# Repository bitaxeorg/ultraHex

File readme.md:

Warning: the bitaxeHex is unfinished. there may be hardware and firmware bugs. Please see The bitaxeHex channel on the [OSMU Discord](https://discord.gg/osmu) for the latest status

> Closed Source is Antithetical to Bitcoin

# Presenting: The bitaxeHex
bitaxeHex is a follow on to the [bitaxe](https://github.com/skot/bitaxe) that incorporates six BM1366 ASICs from the Antminer S19XP

## Goals
- **Standalone**: can mine directly to your pool over WiFi. No External computer needed.
- **Embedded**: low cost, low maintenance, high availability, high reliability, low power.
- **ASIC**: based on the very efficient BM1366 from Bitmain.
- **Versatile**: solo/pool mining, autotune power/heat/efficiency.
- **Open Source**: All design files are provided.

## Features
- **ESP32-S3-WROOM-1** wifi microcontroller on board
- **TI TPS546D24ARVFR** buck regulator steps down the 12V input to power the chain of BM1366
- **TMP1075** measures inlet and outlet PCB temperature.
- **Microchip EMC2302** Controls dual fans
- Header for optional status LCD

## BM1366
- The BM1366 is a undocumented SHA256 mining ASIC from Bitmain. It's mostly used in the Antminer S19XP and S19K Pro
- Bitmain claims the BM1366 has 21.5 W/TH efficiency
- The BM1366 is available (new) for around $15 each.

## Current Status
- v304 is the latest revision but it has a known problem with the Vcore regulator.  There is a workaround, see the bottom of this readme.
- Power draw is around 50W @12V.
- ESP32 miner firmware will configure the power supply to run at the proper voltage.
- This is an _advanced_ build! If you don't have experience building boards, you should probably go build a single ASIC bitaxe first to get the technique down.

## Notes
- Beware that overclocking doesn't produce a higher hash rate on this board, it only causes more heat generation.
- If you decide to build a pre-release board, be sure to order 2 oz. copper on both the internal and external layers.
- The recommended heatsink is not anodized and very conductive on all surfaces. This _should_ be OK as the ASIC tops are not known to be conductive, but this needs some more investigation.

## Revision List
- v304 has a few new minor features, but it has a problem with the Vcore output capacitance.
- v303 has some improvements in the layout and the 33R inline resistors have been removed.
- V302 is the current working version of this board.  If you want to build this, pull down this git tag.
- V301 does not work, the power supply maintains voltage, but overheats in a drastic way
- V300 does not work, the power supply cannot maintain voltage when a load is applied

## Hardware
- [BM1366 from NBTC on AliExpress](https://www.aliexpress.us/item/3256803471845503.html). Both the `AL` and `AG` variants have been known to work.
- [Heatsink](https://www.aliexpress.us/item/3256805608902122.html) 90mm long variant. This will need to have threaded M3 mounting holes added. See the KiCad board file for the pattern
- [Fans](https://www.amazon.com/Noctua-NF-A8-PWM-Premium-Quiet/dp/B00NEMG62M) At least one 80x80mm 12V 4-pin fan. Like the Noctua NF-A8 PWM. Possibly two.
- [Enclosure](https://www.aliexpress.us/item/3256806064761702.html) (several sellers) 130mm long variant. The bitaxeHex needs to be run inside an enclosure to force air through the heatsink and effectively cool the BM1366s
- The TPS546 can potentially benefit from a [small self-adhesive heatsink](https://www.amazon.com/gp/product/B093V6RK58/) on the top of the package.
- All of the parts on the board are listed in the KiCad BOM

## Software
- [ESP-Miner-multichip](https://github.com/bitaxeorg/esp-miner-multichip) a fork of esp-miner to support multiple ASICs like on the bitaxeHex.

## Power Supply Requirements
- bitaxeHex takes 12V DC input via screw terminals. Power supply should be capable of 100W
  - This [120W Brick](https://www.amazon.com/gp/product/B07PWZQ33N) technically works, but gets a little warmer than it should. You'll need to change the end.
  - 12V 15A 110V AliExpress [Bare PSU](https://www.aliexpress.us/item/3256805439916551.html)

## Building
- Check out [building.md](building.md) for PCB ordering tips
- Check out [assembly.md](assembly.md) for assembly tips

## V304 Modification
The Vcore regulator output doesn't have enough bulk capacitance, and the regulator won't run in a stable mode.
In order to fix this, you can hack on a couple 180 uF Aluminium Polymer electrolytic capacitors.  See this diagram for the schematic and part numbers.  The specified parts have wire leads, and you can solder one on each side of the board across the existing ceramic output caps.

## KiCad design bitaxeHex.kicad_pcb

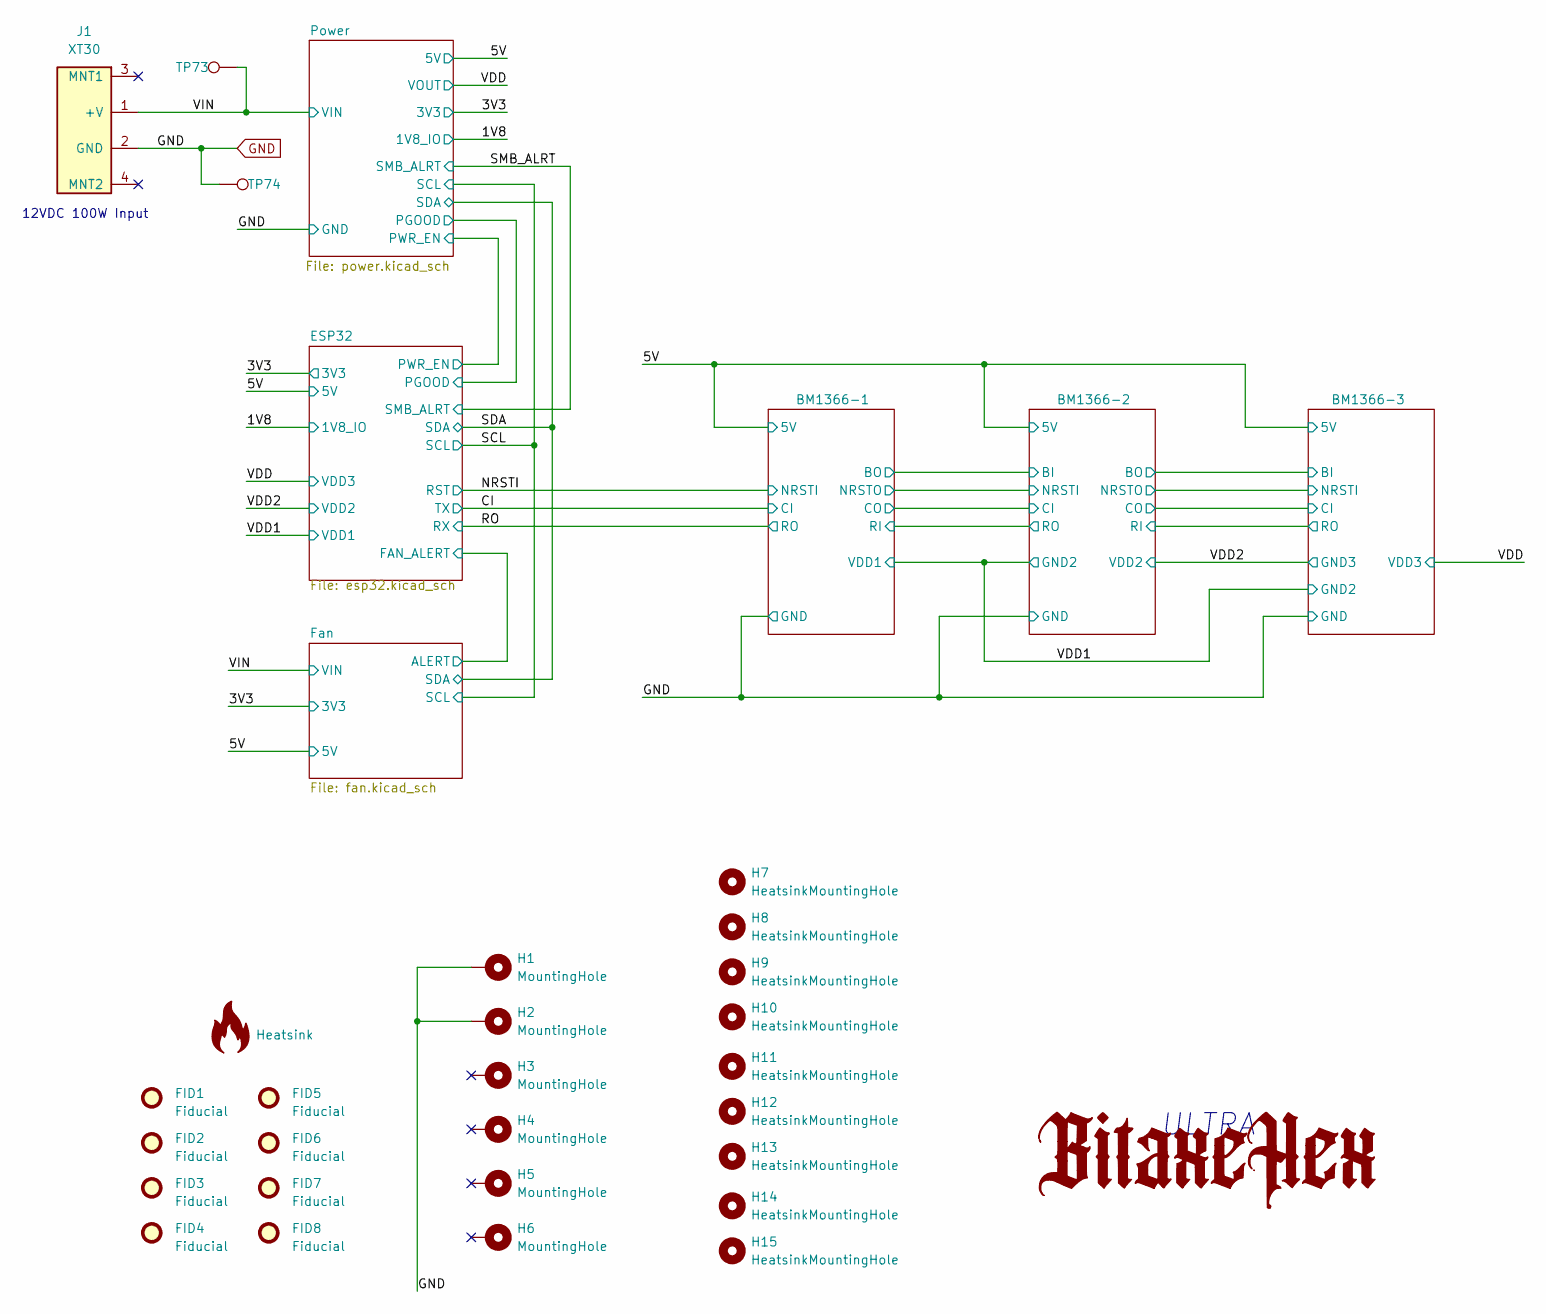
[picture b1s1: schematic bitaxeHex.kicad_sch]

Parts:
FID1, FID2, FID3, FID4, FID5, FID6, FID7, FID8: Fiducial; Fiducial_1mm_Mask2mm
H1, H2, H3, H4, H5, H6: MountingHole; MountingHole_3mm_Pad_Via
H7, H8, H9, H10, H11, H12, H13, H14, H15: HeatsinkMountingHole; 3.1mm_mounting
HS1: Heatsink; hex-heatsink
J1: XT30; XT30PW-M; PARTNO XT30PW-M
TP73, TP74: TestPoint; TestPoint_Pad_D1.0mm

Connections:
/VIN: J1.1 (+V), TP73.1 (1_1); also elsewhere on the board
GND: H1.1 (1_1), H2.1 (1_1), J1.2 (GND), TP74.1 (1_1); also elsewhere on the board

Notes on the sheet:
ULTRA
12VDC 100W Input

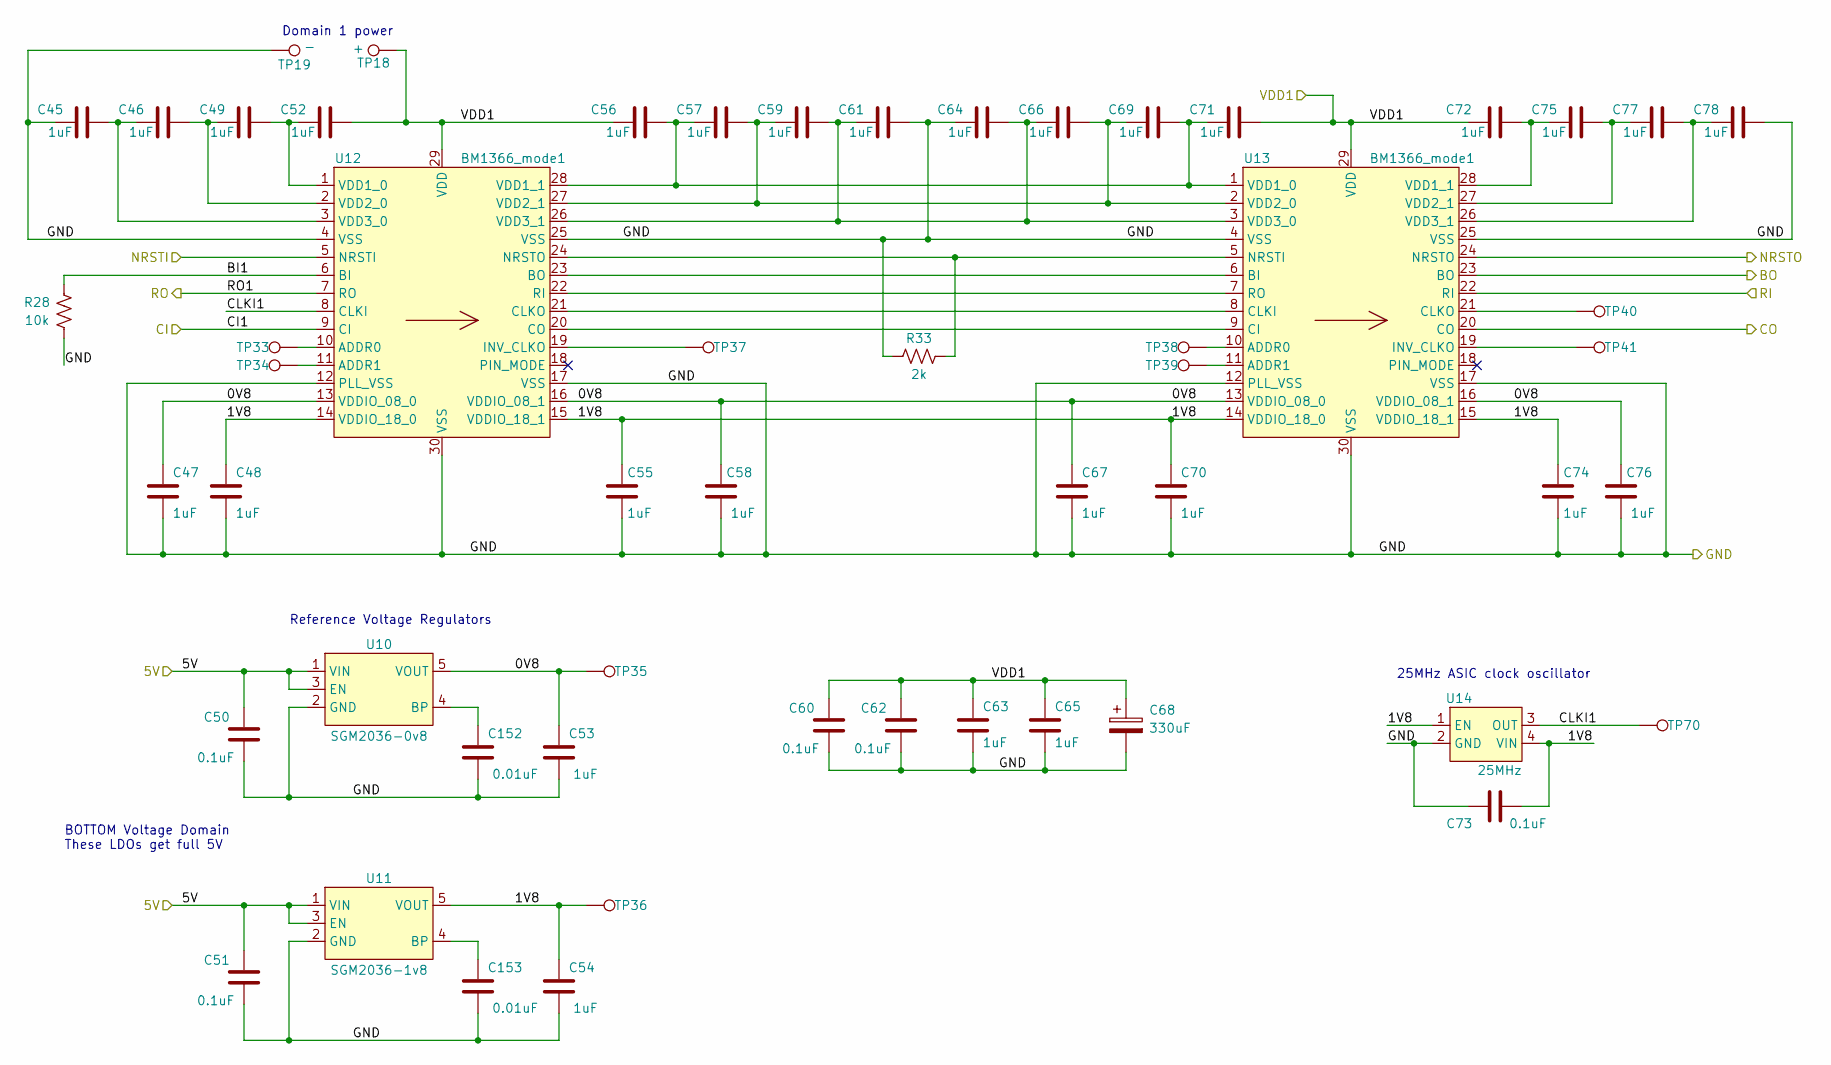
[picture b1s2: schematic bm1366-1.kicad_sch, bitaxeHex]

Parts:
C45, C46, C47, C48, C49, C52, C53, C54, C55, C56, C57, C58, C59, C61, C63, C64, C65, C66, C67, C69, C70, C71, C72, C74, C75, C76, C77, C78: 1uF; C_0402_1005Metric; PARTNO EMK105BJ105MV-F
C50, C51, C60, C62, C73: 0.1uF; C_0402_1005Metric; PARTNO KGM05AR71C104KH
C68: 330uF; CP_EIA-7343-31_Kemet-D_Pad2.25x2.55mm_HandSolder; PARTNO 293D337X9010E2TE3
C152, C153: 0.01uF; C_0402_1005Metric; PARTNO KGM05AR70J103KH
R28: 10k; R_0402_1005Metric; PARTNO RC0402JR-0710KL
R33: 2k; R_0402_1005Metric; PARTNO RT0402BRD072KL
TP18: +; TestPoint_Pad_D1.5mm
TP19: -; TestPoint_Pad_D1.5mm
TP33, TP34, TP37, TP38, TP39, TP40, TP41: TestPoint; TestPoint_Pad_D1.0mm
TP35, TP36, TP70: TestPoint; TestPoint_Pad_D1.0mm_highlight
U10: SGM2036-0v8; TSOT-23-5; PARTNUM SGM2036-0.8YN5G/TR
U11: SGM2036-1v8; TSOT-23-5; PARTNUM SGM2036-1.8YN5G/TR
U12, U13: BM1366_mode1; BM1366
U14: 25MHz; O 25,0-JO32-B-1V3-1-T1-LF; PARTNO O 25,0-JO32-B-1V3-1-T1-LF

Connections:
/5V: C50.2, C51.2, U10.1 (VIN), U10.3 (EN), U11.1 (VIN), U11.3 (EN); also elsewhere on the board
/BM1366-1/0V8: C47.1, C53.1, C58.1, C67.1, C76.1, TP35.1 (1_1), U10.5 (VOUT), U12.13 (VDDIO_08_0), U12.16 (VDDIO_08_1), U13.13 (VDDIO_08_0), U13.16 (VDDIO_08_1)
/BM1366-1/1V8: C48.1, C54.1, C55.1, C70.1, C73.1, C74.1, TP36.1 (1_1), U11.5 (VOUT), U12.14 (VDDIO_18_0), U12.15 (VDDIO_18_1), U13.14 (VDDIO_18_0), U13.15 (VDDIO_18_1), U14.1 (EN), U14.4 (VIN)
/BM1366-1/BI1: R28.2, U12.6 (BI)
/BM1366-1/BO: U13.23 (BO); also elsewhere on the board
/BM1366-1/CLKI1: TP70.1 (1_1), U12.8 (CLKI), U14.3 (OUT)
/BM1366-1/CO: U13.20 (CO); also elsewhere on the board
/BM1366-1/NRSTO: U13.24 (NRSTO); also elsewhere on the board
/BM1366-1/RI: U13.22 (RI); also elsewhere on the board
/CI: U12.9 (CI); also elsewhere on the board
/NRSTI: U12.5 (NRSTI); also elsewhere on the board
/RO: U12.7 (RO); also elsewhere on the board
/VDD1: C52.2, C56.1, C60.2, C62.2, C63.1, C65.1, C68.1, C71.2, C72.1, TP18.1 (1_1), U12.29 (VDD), U13.29 (VDD); also elsewhere on the board
GND: C45.1, C47.2, C48.2, C50.1, C51.1, C53.2, C54.2, C55.2, C58.2, C60.1, C61.2, C62.1, C63.2, C64.1, C65.2, C67.2, C68.2, C70.2, C73.2, C74.2, C76.2, C78.2, C152.2, C153.2, R28.1, R33.1, TP19.1 (1_1), U10.2 (GND), U11.2 (GND), U12.4 (VSS), U12.12 (PLL_VSS), U12.17 (VSS), U12.25 (VSS), U12.30 (VSS), U13.4 (VSS), U13.12 (PLL_VSS), U13.17 (VSS), U13.25 (VSS), U13.30 (VSS), U14.2 (GND); also elsewhere on the board
unnamed: C152.1, U10.4 (BP)
unnamed: C153.1, U11.4 (BP)
unnamed: TP33.1 (1_1), U12.10 (ADDR0)
unnamed: TP34.1 (1_1), U12.11 (ADDR1)
unnamed: U12.23 (BO), U13.6 (BI)
unnamed: U12.21 (CLKO), U13.8 (CLKI)
unnamed: U12.20 (CO), U13.9 (CI)
unnamed: TP37.1 (1_1), U12.19 (INV_CLKO)
unnamed: R33.2, U12.24 (NRSTO), U13.5 (NRSTI)
unnamed: U12.22 (RI), U13.7 (RO)
unnamed: C49.2, C52.1, U12.1 (VDD1_0)
unnamed: C56.2, C57.1, C69.2, C71.1, U12.28 (VDD1_1), U13.1 (VDD1_0)
unnamed: C46.2, C49.1, U12.2 (VDD2_0)
unnamed: C57.2, C59.1, C66.2, C69.1, U12.27 (VDD2_1), U13.2 (VDD2_0)
unnamed: C45.2, C46.1, U12.3 (VDD3_0)
unnamed: C59.2, C61.1, C64.2, C66.1, U12.26 (VDD3_1), U13.3 (VDD3_0)
unnamed: TP38.1 (1_1), U13.10 (ADDR0)
unnamed: TP39.1 (1_1), U13.11 (ADDR1)
unnamed: TP40.1 (1_1), U13.21 (CLKO)
unnamed: TP41.1 (1_1), U13.19 (INV_CLKO)
unnamed: C72.2, C75.1, U13.28 (VDD1_1)
unnamed: C75.2, C77.1, U13.27 (VDD2_1)
unnamed: C77.2, C78.1, U13.26 (VDD3_1)

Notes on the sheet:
Reference Voltage Regulators
BOTTOM Voltage Domain These LDOs get full 5V
Domain 1 power
25MHz ASIC clock oscillator

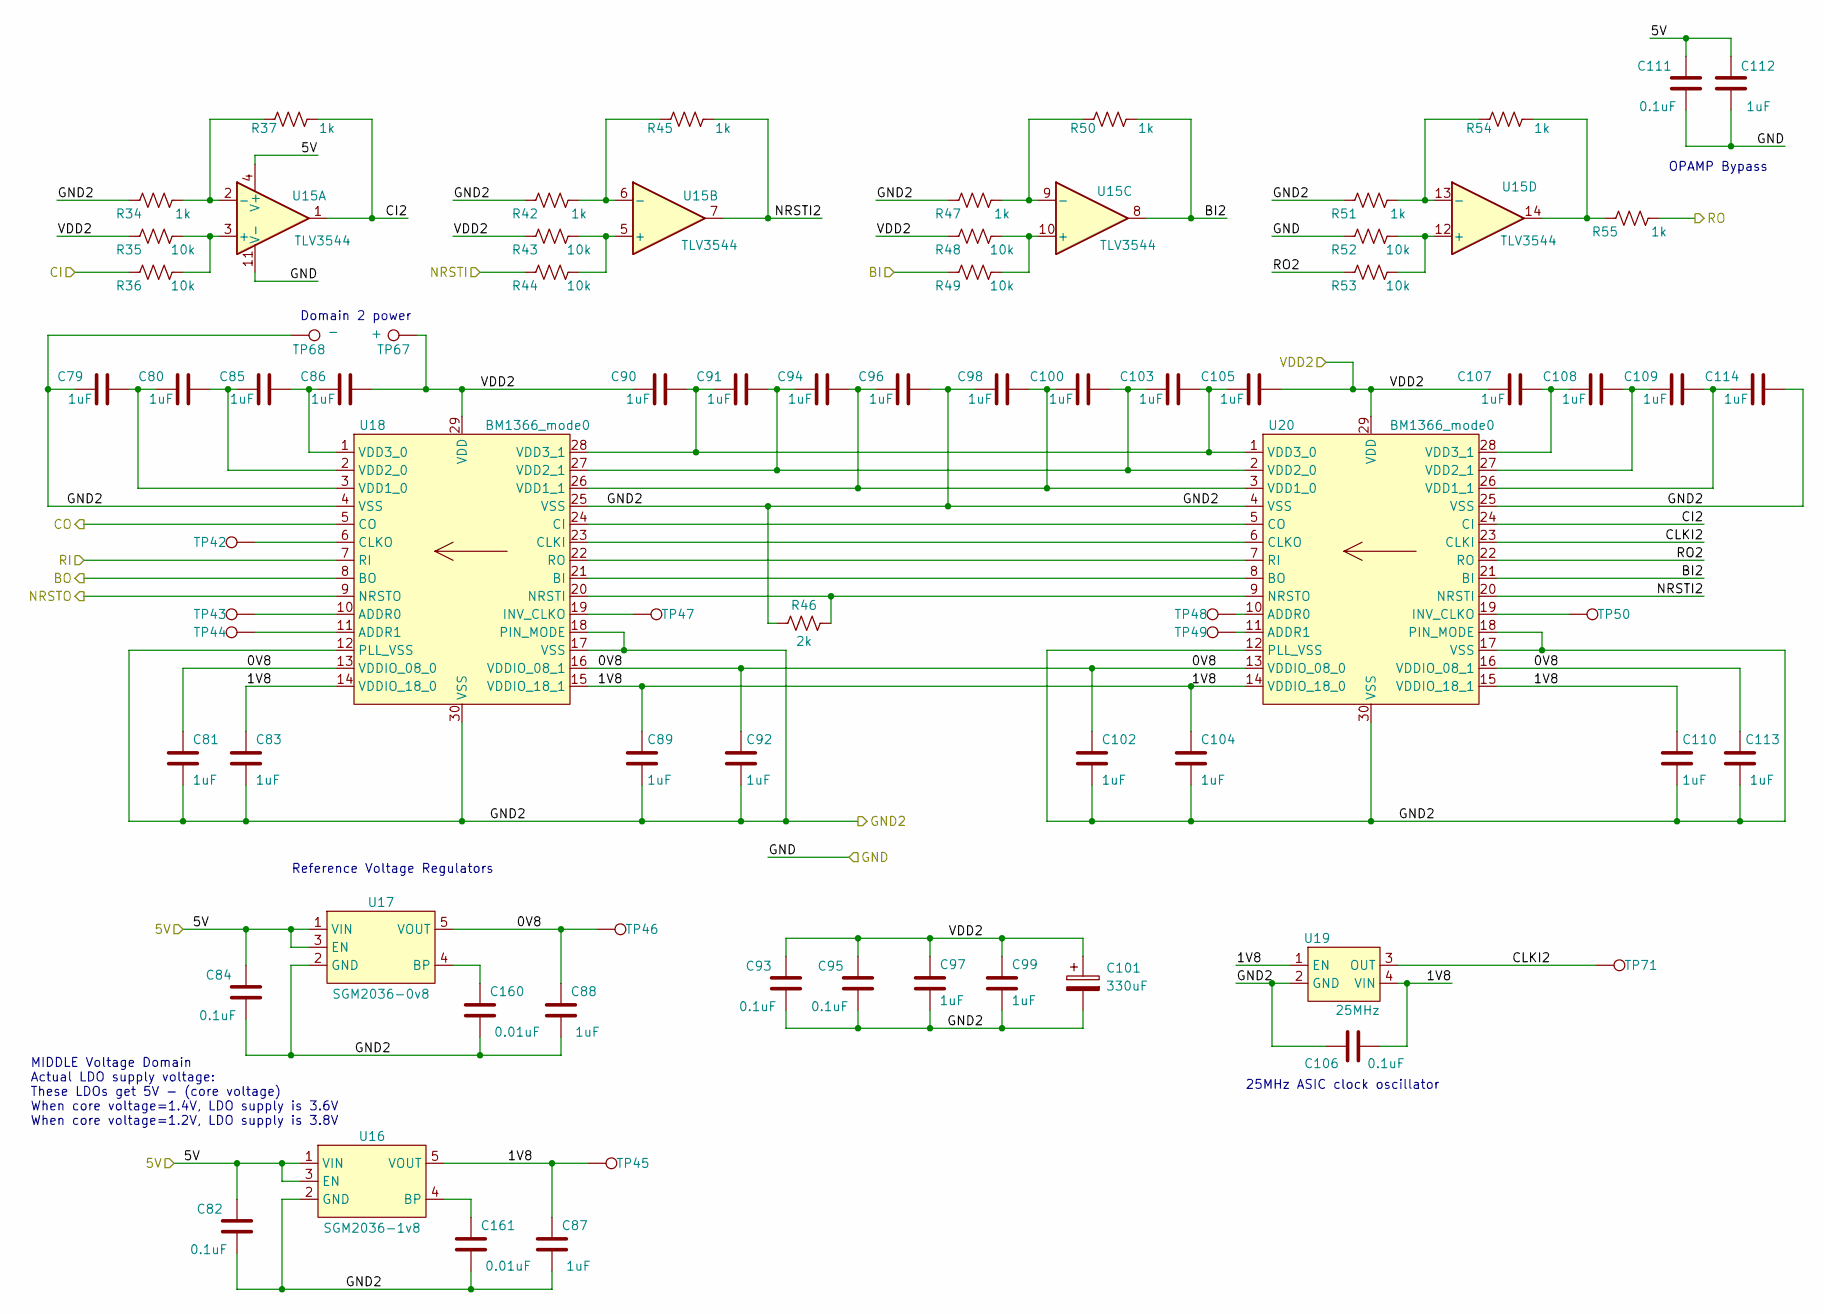
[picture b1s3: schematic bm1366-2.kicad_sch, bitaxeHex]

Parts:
C79, C80, C81, C83, C85, C86, C87, C88, C89, C90, C91, C92, C94, C96, C97, C98, C99, C100, C102, C103, C104, C105, C107, C108, C109, C110, C112, C113, C114: 1uF; C_0402_1005Metric; PARTNO EMK105BJ105MV-F
C82, C84, C93, C95, C106, C111: 0.1uF; C_0402_1005Metric; PARTNO KGM05AR71C104KH
C101: 330uF; CP_EIA-7343-31_Kemet-D_Pad2.25x2.55mm_HandSolder; PARTNO 293D337X9010E2TE3
C160, C161: 0.01uF; C_0402_1005Metric; PARTNO KGM05AR70J103KH
R34, R37, R42, R45, R47, R50, R51, R54, R55: 1k; R_0402_1005Metric; PARTNO RC0402FR-071KL
R35, R36, R43, R44, R48, R49, R52, R53: 10k; R_0402_1005Metric; PARTNO RC0402JR-0710KL
R46: 2k; R_0402_1005Metric; PARTNO RT0402BRD072KL
TP42, TP43, TP44, TP47, TP48, TP49, TP50: TestPoint; TestPoint_Pad_D1.0mm
TP45, TP46, TP71: TestPoint; TestPoint_Pad_D1.0mm_highlight
TP67: +; TestPoint_Pad_D1.5mm
TP68: -; TestPoint_Pad_D1.5mm
U15: TLV3544; TSSOP-14_4.4x5mm_P0.65mm; PARTNO TLV3544IPWR
U16: SGM2036-1v8; TSOT-23-5; PARTNUM SGM2036-1.8YN5G/TR
U17: SGM2036-0v8; TSOT-23-5; PARTNUM SGM2036-0.8YN5G/TR
U18, U20: BM1366_mode0; BM1366
U19: 25MHz; O 25,0-JO32-B-1V3-1-T1-LF; PARTNO O 25,0-JO32-B-1V3-1-T1-LF

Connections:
/5V: C82.2, C84.2, C111.2, C112.2, U15.4 (V+), U16.1 (VIN), U16.3 (EN), U17.1 (VIN), U17.3 (EN); also elsewhere on the board
/BM1366-1/BO: R49.1; also elsewhere on the board
/BM1366-1/CO: R36.1; also elsewhere on the board
/BM1366-1/NRSTO: R44.1; also elsewhere on the board
/BM1366-1/RI: R55.1; also elsewhere on the board
/BM1366-2/0V8: C81.1, C88.1, C92.1, C102.1, C113.1, TP46.1 (1_1), U17.5 (VOUT), U18.13 (VDDIO_08_0), U18.16 (VDDIO_08_1), U20.13 (VDDIO_08_0), U20.16 (VDDIO_08_1)
/BM1366-2/1V8: C83.1, C87.1, C89.1, C104.1, C106.1, C110.1, TP45.1 (1_1), U16.5 (VOUT), U18.14 (VDDIO_18_0), U18.15 (VDDIO_18_1), U19.1 (EN), U19.4 (VIN), U20.14 (VDDIO_18_0), U20.15 (VDDIO_18_1)
/BM1366-2/BI2: R50.1, U15.8, U20.21 (BI)
/BM1366-2/BO: U18.8 (BO); also elsewhere on the board
/BM1366-2/CI2: R37.1, U15.1, U20.24 (CI)
/BM1366-2/CLKI2: TP71.1 (1_1), U19.3 (OUT), U20.23 (CLKI)
/BM1366-2/CO: U18.5 (CO); also elsewhere on the board
/BM1366-2/NRSTI2: R45.1, U15.7, U20.20 (NRSTI)
/BM1366-2/NRSTO: U18.9 (NRSTO); also elsewhere on the board
/BM1366-2/RI: U18.7 (RI); also elsewhere on the board
/BM1366-2/RO2: R53.1, U20.22 (RO)
/VDD1: C79.1, C81.2, C82.1, C83.2, C84.1, C87.2, C88.2, C89.2, C92.2, C93.1, C95.1, C96.2, C97.2, C98.1, C99.2, C101.2, C102.2, C104.2, C106.2, C110.2, C113.2, C114.2, C160.2, C161.2, R34.2, R42.2, R46.1, R47.2, R51.2, TP68.1 (1_1), U16.2 (GND), U17.2 (GND), U18.4 (VSS), U18.12 (PLL_VSS), U18.17 (VSS), U18.18 (PIN_MODE), U18.25 (VSS), U18.30 (VSS), U19.2 (GND), U20.4 (VSS), U20.12 (PLL_VSS), U20.17 (VSS), U20.18 (PIN_MODE), U20.25 (VSS), U20.30 (VSS); also elsewhere on the board
/VDD2: C86.2, C90.1, C93.2, C95.2, C97.1, C99.1, C101.1, C105.2, C107.1, R35.2, R43.1, R48.1, TP67.1 (1_1), U18.29 (VDD), U20.29 (VDD); also elsewhere on the board
GND: C111.1, C112.1, R52.1, U15.11 (V-); also elsewhere on the board
unnamed: R54.1, R55.2, U15.14
unnamed: R35.1, R36.2, U15.3 (+)
unnamed: R34.1, R37.2, U15.2 (-)
unnamed: R43.2, R44.2, U15.5 (+)
unnamed: R42.1, R45.2, U15.6 (-)
unnamed: R48.2, R49.2, U15.10 (+)
unnamed: R47.1, R50.2, U15.9 (-)
unnamed: R52.2, R53.2, U15.12 (+)
unnamed: R51.1, R54.2, U15.13 (-)
unnamed: C161.1, U16.4 (BP)
unnamed: C160.1, U17.4 (BP)
unnamed: TP43.1 (1_1), U18.10 (ADDR0)
unnamed: TP44.1 (1_1), U18.11 (ADDR1)
unnamed: U18.21 (BI), U20.8 (BO)
unnamed: U18.24 (CI), U20.5 (CO)
unnamed: U18.23 (CLKI), U20.6 (CLKO)
unnamed: TP42.1 (1_1), U18.6 (CLKO)
unnamed: TP47.1 (1_1), U18.19 (INV_CLKO)
unnamed: R46.2, U18.20 (NRSTI), U20.9 (NRSTO)
unnamed: U18.22 (RO), U20.7 (RI)
unnamed: C79.2, C80.1, U18.3 (VDD1_0)
unnamed: C94.2, C96.1, C98.2, C100.1, U18.26 (VDD1_1), U20.3 (VDD1_0)
unnamed: C80.2, C85.1, U18.2 (VDD2_0)
unnamed: C91.2, C94.1, C100.2, C103.1, U18.27 (VDD2_1), U20.2 (VDD2_0)
unnamed: C85.2, C86.1, U18.1 (VDD3_0)
unnamed: C90.2, C91.1, C103.2, C105.1, U18.28 (VDD3_1), U20.1 (VDD3_0)
unnamed: TP48.1 (1_1), U20.10 (ADDR0)
unnamed: TP49.1 (1_1), U20.11 (ADDR1)
unnamed: TP50.1 (1_1), U20.19 (INV_CLKO)
unnamed: C109.2, C114.1, U20.26 (VDD1_1)
unnamed: C108.2, C109.1, U20.27 (VDD2_1)
unnamed: C107.2, C108.1, U20.28 (VDD3_1)

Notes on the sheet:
Domain 2 power
MIDDLE Voltage Domain Actual LDO supply voltage: These LDOs get 5V - (core voltage) When core voltage=1.4V, LDO supply is 3.6V When core voltage=1.2V, LDO supply is 3.8V
Reference Voltage Regulators
25MHz ASIC clock oscillator
OPAMP Bypass

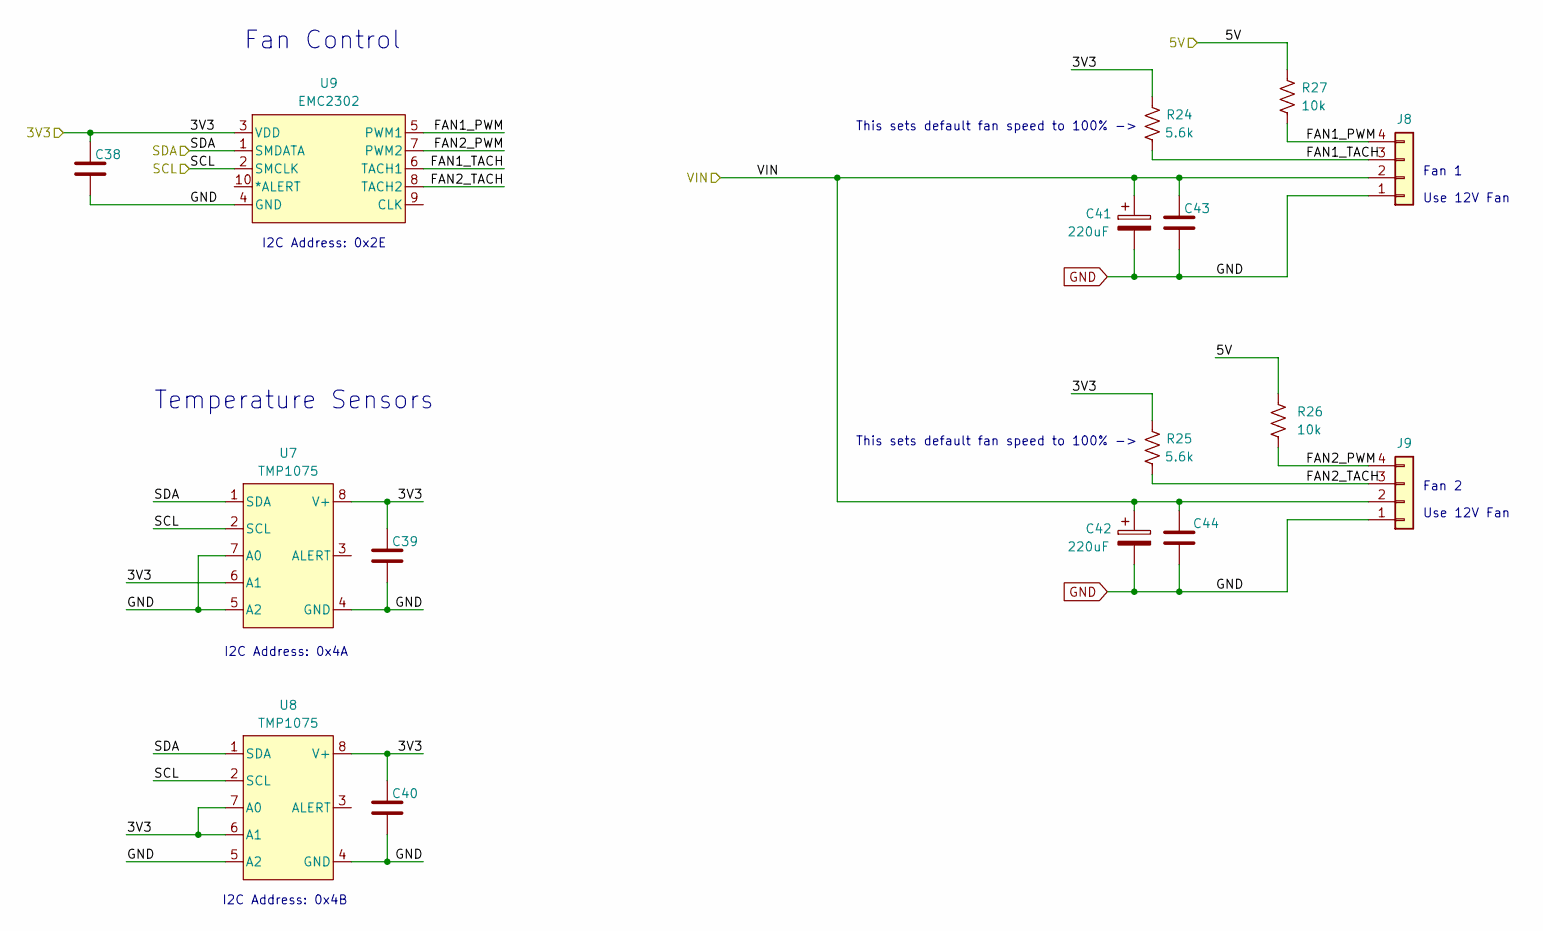
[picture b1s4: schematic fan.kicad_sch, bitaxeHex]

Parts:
C38, C39, C40, C43, C44: 311-3342-1-ND; C_0402_1005Metric; PARTNO KGM05AR71C104KH
C41, C42: 220uF; CP_Elec_6.3x7.7; PARTNO 865080345012
J8, J9: Conn_01x04; 470531000; PARTNO 0470531000
R24, R25: 5.6k; R_0402_1005Metric; PARTNO RC0402FR-135K6L
R26, R27: 10k; R_0402_1005Metric; PARTNO RC0402JR-0710KL
U7, U8: TMP1075; HVSSOP-8_3x3mm_P0.65mm; PARTNO TMP1075DGKR
U9: EMC2302; MSOP-10_3x3mm_P0.5mm; PARTNO EMC2302-2-AIZL-TR

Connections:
/3V3: C38.1, C39.1, C40.1, R24.2, R25.2, U7.6 (A1), U7.8 (V+), U8.6 (A1), U8.7 (A0), U8.8 (V+), U9.3 (VDD); also elsewhere on the board
/5V: R26.2, R27.2; also elsewhere on the board
/Fan/FAN1_PWM: J8.4, R27.1, U9.5 (PWM1)
/Fan/FAN1_TACH: J8.3, R24.1, U9.6 (TACH1)
/Fan/FAN2_PWM: J9.4, R26.1, U9.7 (PWM2)
/Fan/FAN2_TACH: J9.3, R25.1, U9.8 (TACH2)
/SCL: U7.2 (SCL), U8.2 (SCL), U9.2 (SMCLK); also elsewhere on the board
/SDA: U7.1 (SDA), U8.1 (SDA), U9.1 (SMDATA); also elsewhere on the board
/VIN: C41.1, C42.1, C43.1, C44.1, J8.2, J9.2; also elsewhere on the board
GND: C38.2, C39.2, C40.2, C41.2, C42.2, C43.2, C44.2, J8.1, J9.1, U7.4 (GND), U7.5 (A2), U7.7 (A0), U8.4 (GND), U8.5 (A2), U9.4 (GND); also elsewhere on the board

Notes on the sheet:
I2C Address: 0x2E
Temperature Sensors
I2C Address: 0x4A
Fan Control
Fan 1
Use 12V Fan
This sets default fan speed to 100% ->
Fan 2
I2C Address: 0x4B

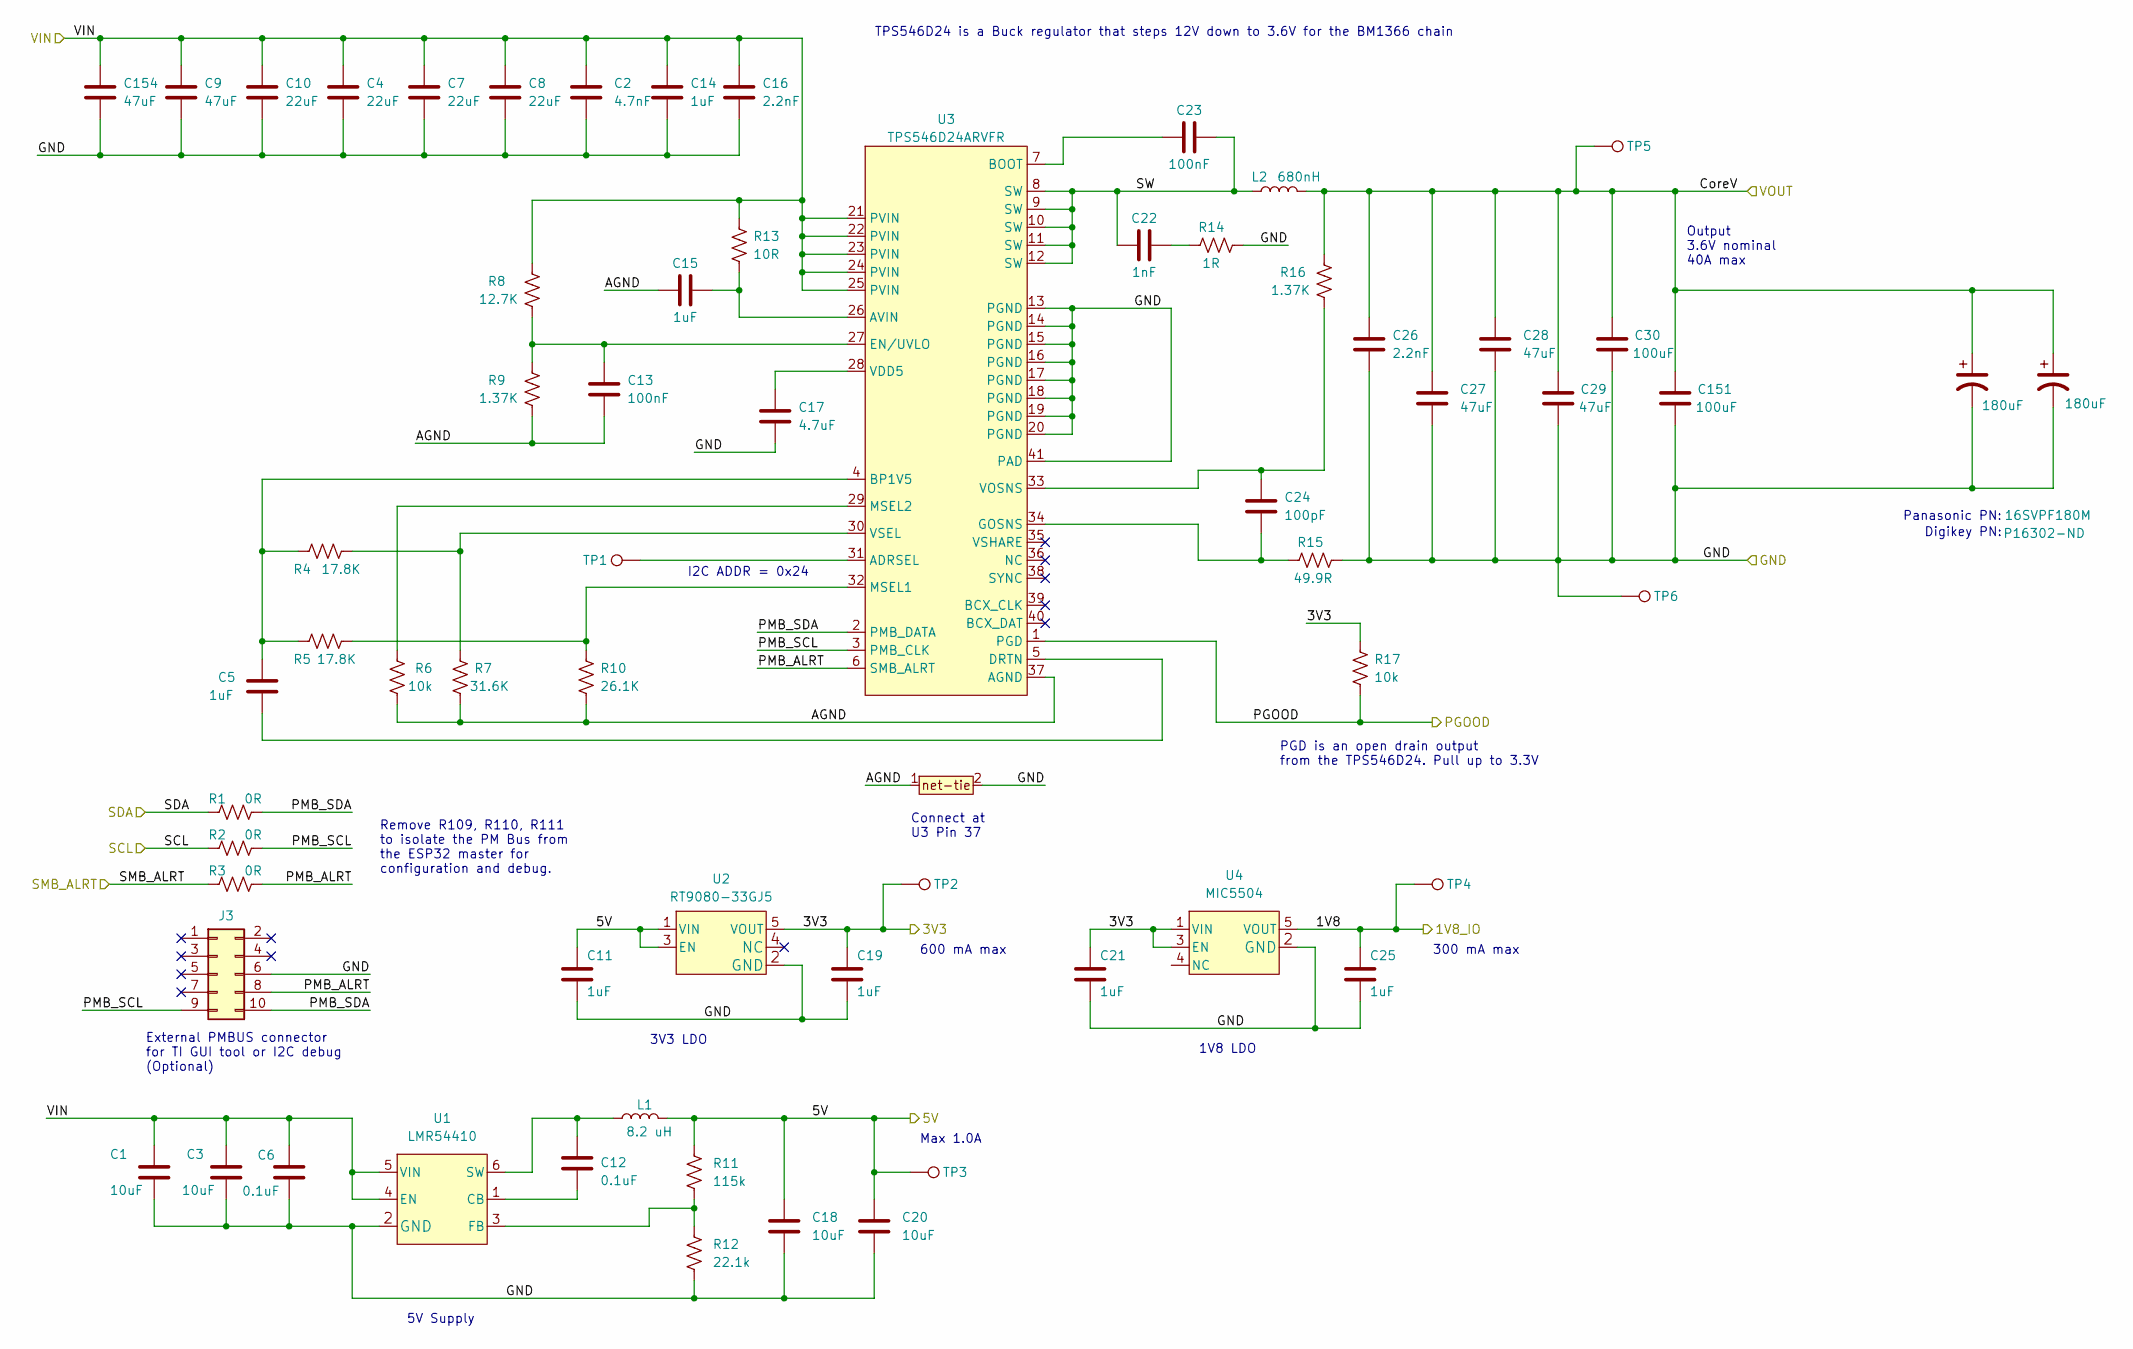
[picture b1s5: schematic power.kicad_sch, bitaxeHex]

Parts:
C1, C3, C18, C20: 10uF; C_0805_2012Metric; PARTNO GRM21BR61H106ME43L
C2: 4.7nF; C_0402_1005Metric; PARTNO GRM155R71E472KA01D
C4, C7, C8, C10: 22uF; C_1206_3216Metric; PARTNO C3216X5R1E226M160AB
C5: 1uF; C_0603_1608Metric; PARTNO GRM188R60J105KA01D
C6: 0.1uF; C_0603_1608Metric; PARTNO KGM15BR71H104KT
C9, C154: 47uF; C_1206_3216Metric; PARTNO C3216X5R1E476M160DC
C11, C19, C21, C25: 1uF; C_0402_1005Metric; PARTNO EMK105BJ105MV-F
C12: 0.1uF; C_0402_1005Metric; PARTNO KGM05AR71C104KH
C13: 100nF; C_0402_1005Metric; PARTNO GRM155R71A104KA01D
C14, C15: 1uF; C_0805_2012Metric; PARTNO TMK212BJ105KG-T
C16, C26: 2.2nF; C_0402_1005Metric; PARTNO GRM155R61H222KA01D
C17: 4.7uF; C_0402_1005Metric; PARTNO GRM155R61A475MEAAD
C22: 1nF; C_0805_2012Metric; PARTNO CC0805KRX7R9BB102
C23: 100nF; C_0805_2012Metric; PARTNO KGM21NR71E104KT
C24: 100pF; C_0402_1005Metric; PARTNO 885012005013
C27, C28, C29: 47uF; C_1210_3225Metric; PARTNO C3225X5R0J476M250AA
C30, C151: 100uF; C_1210_3225Metric; PARTNO GRM32EE70J107ME15L
C155: 180uF; PARTNO 16SVPF180M
C156: 180uF
J3: Conn_02x05_Odd_Even; PinHeader_2x05_P2.54mm_Vertical
L1: 8.2 uH; 74438357082; PARTNO 78438357082
L2: 680nH; L_Coilcraft_XAL1010-XXX; PARTNO XAL1010-681MED; Mouser 994-XAL1010-681MED
R1, R2, R3: 0R; R_0402_1005Metric; PARTNO RC0402JR-070RL
R4, R5: 17.8K; R_0402_1005Metric; PARTNO RMCF0402FT17K8
R6: 10k; R_0402_1005Metric; PARTNO RMCF0402FT10K0
R7: 31.6K; R_0402_1005Metric; PARTNO RC0402FR-0731K6L
R8: 12.7K; R_0402_1005Metric; PARTNO RC0402FR-0712K7L
R9, R16: 1.37K; R_0402_1005Metric; PARTNO RC0402FR-071K37L
R10: 26.1K; R_0402_1005Metric; PARTNO RC0402FR-0726K1L
R11: 115k; R_0402_1005Metric; PARTNO RC0402FR-07115KL
R12: 22.1k; R_0402_1005Metric; PARTNO RC0402FR-0722K1L
R13: 10R; R_0402_1005Metric; PARTNO RC0402FR-0710RL
R14: 1R; R_1206_3216Metric; PARTNO CSR1206FT1R00
R15: 49.9R; R_0402_1005Metric; PARTNO RC0402FR-0749R9L
R17: 10k; R_0402_1005Metric; PARTNO RC0402JR-0710KL
T1: net-tie; Net-Tie-0.25mm
TP1: TestPoint; TestPoint_Pad_D0.8mm
TP2, TP3, TP4, TP5, TP6: TestPoint; TestPoint_Pad_D1.0mm
U1: LMR54410; SOT-23-6; PARTNO LMR54410FDBVR
U2: RT9080-33GJ5; PARTNO RT9080-33GJ5
U3: TPS546D24ARVFR; LQFN40-CLIP; PARTNO TPS546D24ARVFR
U4: MIC5504; SOT-23-5_HandSoldering; PARTNO MIC5504-1.8YM5-TR

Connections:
/1V8: C25.1, TP4.1 (1_1), U4.5 (VOUT); also elsewhere on the board
/3V3: C19.1, C21.1, R17.2, TP2.1 (1_1), U2.5 (VOUT), U4.1 (VIN), U4.3 (EN); also elsewhere on the board
/5V: C11.1, C18.1, C20.1, L1.2, R11.1, TP3.1 (1_1), U2.1 (VIN), U2.3 (EN); also elsewhere on the board
/Power/AGND: C13.2, C15.1, R6.1, R7.2, R9.2, R10.2, T1.1, U3.37 (AGND)
/Power/PGOOD: R17.1, U3.1 (PGD); also elsewhere on the board
/Power/PMB_ALRT: J3.8, R3.2, U3.6 (SMB_ALRT)
/Power/PMB_SCL: J3.9, R2.2, U3.3 (PMB_CLK)
/Power/PMB_SDA: J3.10, R1.2, U3.2 (PMB_DATA)
/Power/SW: C22.1, C23.2, L2.1, U3.8 (SW), U3.9 (SW), U3.10 (SW), U3.11 (SW), U3.12 (SW)
/SCL: R2.1; also elsewhere on the board
/SDA: R1.1; also elsewhere on the board
/SMB_ALRT: R3.1; also elsewhere on the board
/VDD: C26.1, C27.1, C28.1, C29.1, C30.1, C151.1, C155.1, C156.1, L2.2, R16.1, TP5.1 (1_1); also elsewhere on the board
/VIN: C1.1, C2.1, C3.1, C4.1, C6.2, C7.1, C8.1, C9.1, C10.1, C14.1, C16.1, C154.1, R8.1, R13.1, U1.4 (EN), U1.5 (VIN), U3.21 (PVIN), U3.22 (PVIN), U3.23 (PVIN), U3.24 (PVIN), U3.25 (PVIN); also elsewhere on the board
GND: C1.2, C2.2, C3.2, C4.2, C6.1, C7.2, C8.2, C9.2, C10.2, C11.2, C14.2, C16.2, C17.2, C18.2, C19.2, C20.2, C21.2, C25.2, C26.2, C27.2, C28.2, C29.2, C30.2, C151.2, C154.2, J3.6, R12.2, R14.2, R15.2, TP6.1 (1_1), U1.2 (GND), U2.2 (GND), U3.13 (PGND), U3.14 (PGND), U3.15 (PGND), U3.16 (PGND), U3.17 (PGND), U3.18 (PGND), U3.19 (PGND), U3.20 (PGND), U3.41 (PAD), U4.2 (GND); also elsewhere on the board
unnamed: C22.2, R14.1
unnamed: C12.2, U1.1 (CB)
unnamed: R11.2, R12.1, U1.3 (FB)
unnamed: C12.1, L1.1, U1.6 (SW)
unnamed: TP1.1 (1_1), U3.31 (ADRSEL)
unnamed: C15.2, R13.2, U3.26 (AVIN)
unnamed: C23.1, U3.7 (BOOT)
unnamed: C5.1, R4.1, R5.1, U3.4 (BP1V5)
unnamed: C5.2, U3.5 (DRTN)
unnamed: C13.1, R8.2, R9.1, U3.27 (EN/UVLO)
unnamed: C24.2, R15.1, U3.34 (GOSNS)
unnamed: R5.2, R10.1, U3.32 (MSEL1)
unnamed: R6.2, U3.29 (MSEL2)
unnamed: C17.1, U3.28 (VDD5)
unnamed: C24.1, R16.2, U3.33 (VOSNS)
unnamed: R4.2, R7.1, U3.30 (VSEL)

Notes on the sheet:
1V8 LDO
Output 3.6V nominal 40A max
TPS546D24 is a Buck regulator that steps 12V down to 3.6V for the BM1366 chain
3V3 LDO
300 mA max
Remove R109, R110, R111 to isolate the PM Bus from the ESP32 master for configuration and debug.
Max 1.0A
Connect at U3 Pin 37
External PMBUS connector for TI GUI tool or I2C debug (Optional)
600 mA max
5V Supply
Digikey PN:
PGD is an open drain output from the TPS546D24. Pull up to 3.3V
I2C ADDR = 0x24
Panasonic PN:
